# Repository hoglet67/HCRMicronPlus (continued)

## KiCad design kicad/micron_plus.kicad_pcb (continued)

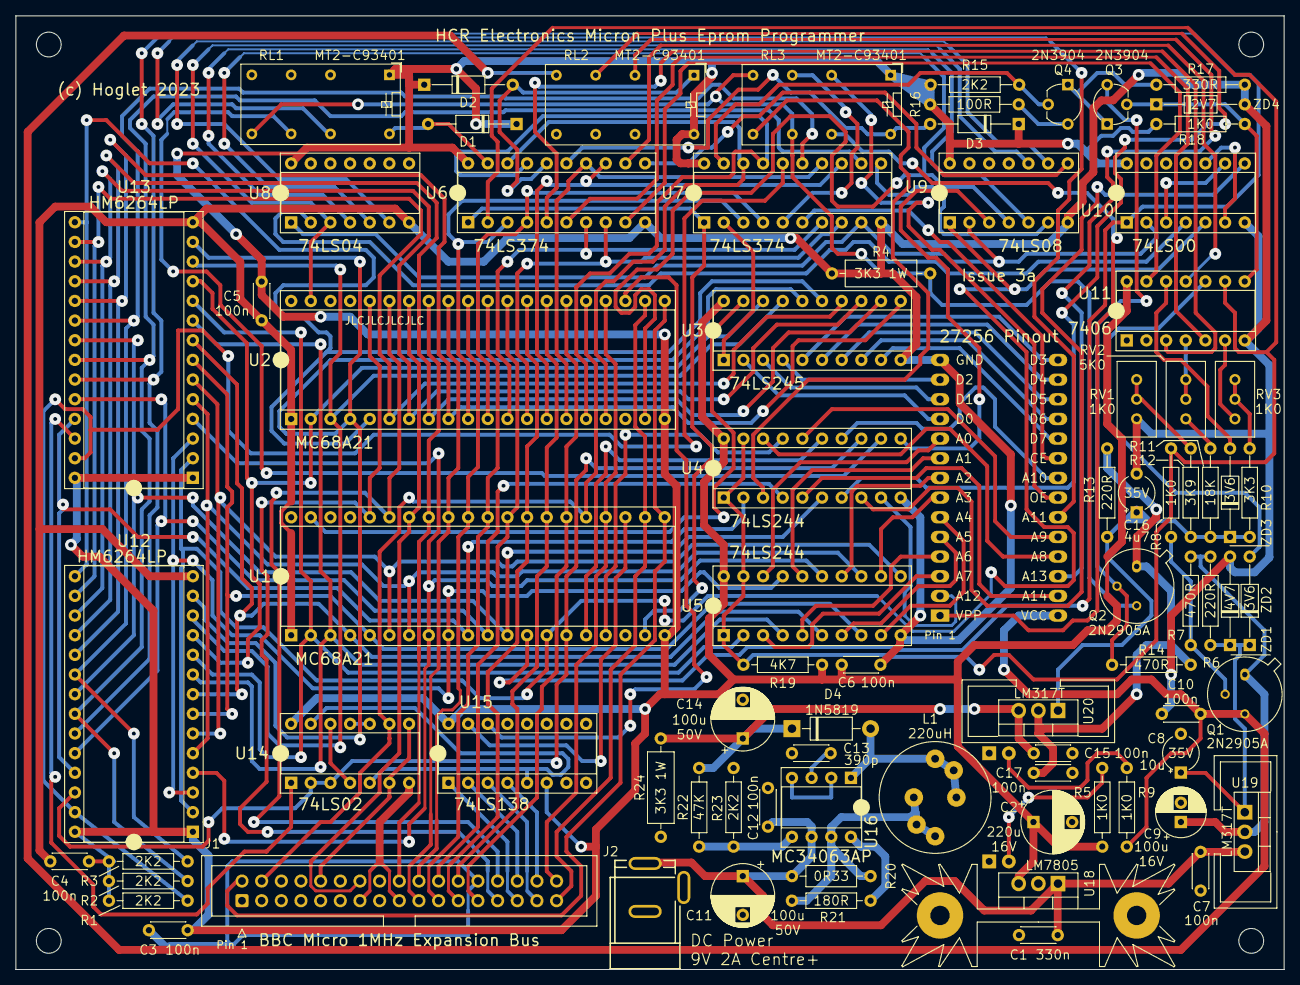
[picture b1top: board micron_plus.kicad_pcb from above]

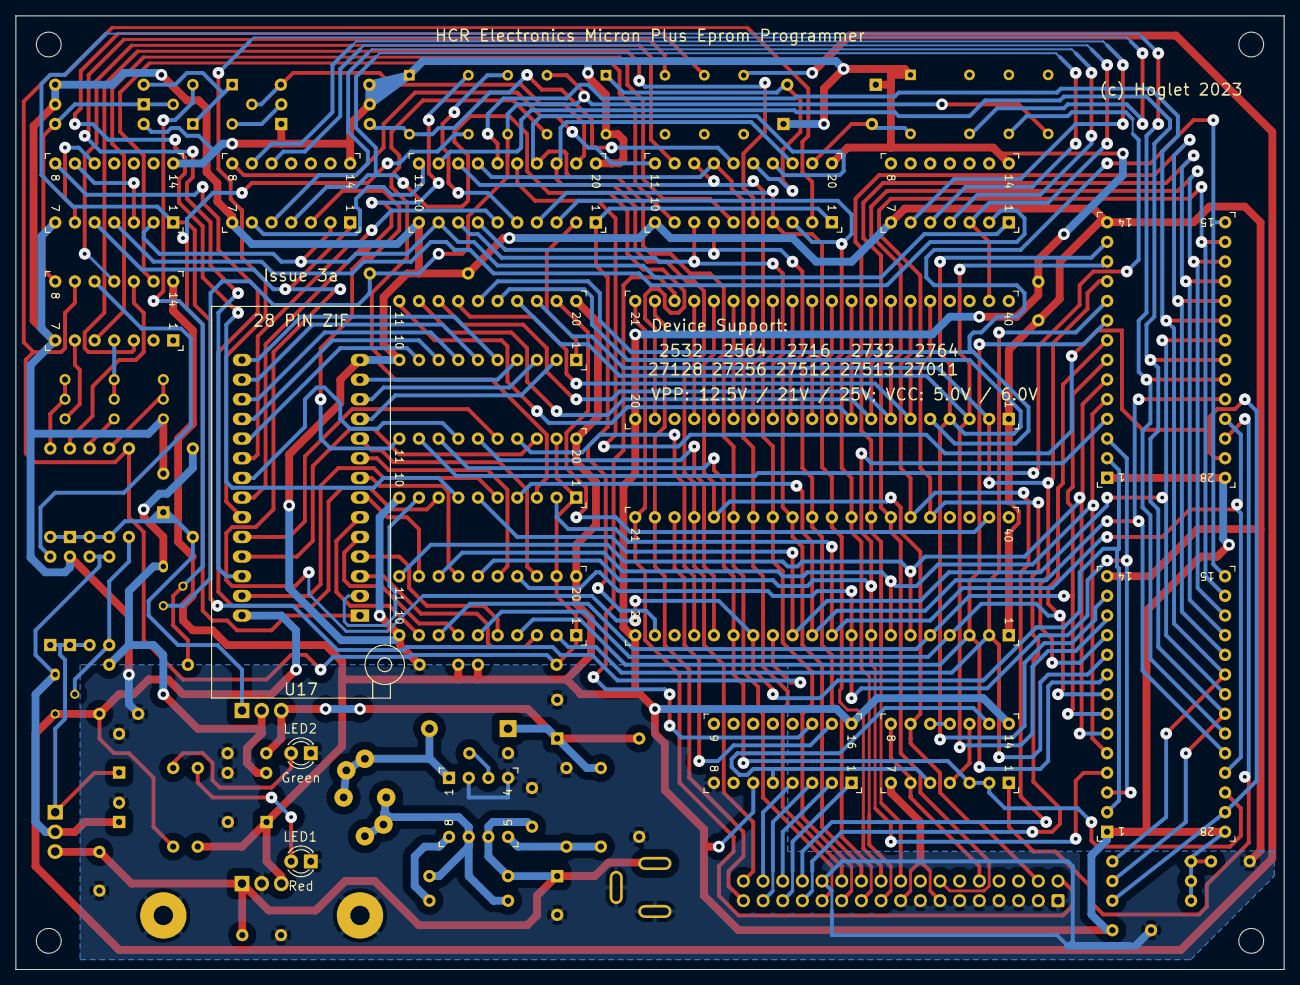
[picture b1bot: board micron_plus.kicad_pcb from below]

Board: 2 copper layers, 163.8 x 123.2 mm, 91 parts (3 on the bottom side), 144 nets.

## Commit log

2023-10-28 Initial KiCAD schematic
2023-10-28 Move 7406 onto PSU sheet
2023-10-28 Update PDF version
2023-10-28 Checked in initial version of disassembly
2023-10-28 KiCAD: Use just one nVCCEnable connector on PSU sheet
2023-10-29 Fixed following stardot discussion of PSU, and review of issue 2 photos
2023-11-01 KiCAD: Initial PCB placement
2023-11-04 KiCAD: PCB now routed
2023-11-04 KiCAD: Tidying errors/warnings
2023-11-04 KiCAD: Adjust courtyards
2023-11-04 KiCAD: Custom DRC rule to ignore transformer courtyard (for now)
2023-11-04 KiCAD: Added R19 (VCCEnable pullup)
2023-11-08 KiCAD: Replace transition header with normal pin header
2023-11-09 KiCAD: Replace transformer with DC Jack + Boost Converter
2023-11-09 KiCAD: Tweak boost convertor values
2023-11-09 KiCAD: Add heatsinks
2023-11-09 KiCAD: Trimmers now Bourns 3296W
2023-11-09 KiCAD: Refresh PDF
2023-11-15 KiCAD: Custom footprint for inductor with multiple pads
2023-11-15 KiCAD - silk screen
2023-11-15 KiCAD - more silk screen
2023-11-16 KiCAD: Customize IC footprint silk screen
2023-11-16 KiCAD: Use 0.95mm holes for ZIF socket
2023-11-16 KiCAD: silk screen
2023-11-16 KiCAD: larger footprint for 1W resistors
2023-11-16 Disassembly: commit latest asm file
2023-11-17 KiCAD: Make space for full ZIF
2023-11-17 KiCAD: Add 100n close to MC34063A
2023-11-18 KiCAD: DC Jack now flush with board edge
2023-11-18 KiCAD: larger 0R33; silk screen
2023-11-18 KiCAD: Allow space for box header for 1MHz bus
2023-11-18 KiCAD: Tiny tweaks
2023-11-19 KiCAD: Improve ground routing
2023-11-19 KiCAD: Holes now M3, inset 4.25mm X and 3.7mm Y
2023-11-20 KiCAD: Add JLCJLCJLCJLC
2023-11-20 KiCAD: Add (c) Hoglet
2023-11-20 KiCAD: Setup Solder Mask Clearance for JLC
2023-11-20 KiCAD: Move JLCJLCJLCJLC
2023-11-20 KiCAD: Minor silk screen changes
2023-11-20 KiCAD: Via holes now 0.5mm/0.7mm
2023-11-20 KiCAD: Minor track spacing
2023-11-20 KiCAD: Reverse D1/2
2023-11-20 KiCAD: Increase ZIF hole size to 0.95mm
2023-11-20 KiCAD: Add gerbers
2023-12-06 Firmware: Initial 1.41 version
2023-12-06 Firmware: Version 1.42 and comments
2023-12-06 Firmware: minor built change
2023-12-06 Firmware: Correctly sequence VCC/VPP for 24-pin EPROMs
2023-12-07 Firmware: 27256/27128/2764 add delay to allow VPP to stablize
